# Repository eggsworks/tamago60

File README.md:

# tamago60

tamago60 is a hotswap, semi-split, low profile, ortholinear keyboard with a joystick in the middle.

## PCBWay

PCB prototyping for the tamago60 was kindly sponsored by [PCBWay](https://www.pcbway.com/). If you choose to build your own
tamago60, consider ordering from [PCBWay](https://www.pcbway.com/) to experience their fast turnaround, high quality production,
and excellent customer service. Thanks, PCBWay!

I've also shared this design on their site to make it really
easy to order your own board:

## Overview

We all love those laptops with the trackpoint in the middle of the keyboard, right? Influenced by that design,
with an ergo twist and a healthy dose of minimalism, the tamago60 is a roughly-60% board with a joystick
stuck between two semi-split ortho halves.

This design uses MX spacing (19mm) to allow flexibility with choice of keycaps. For the same reason, switches are
installed directly to the PCB rather than into a switchplate (DSA keycaps will crash into the plate if used with
Choc V2's).

## Components

- 60-64 Kailh Choc hotswap sockets
  - Depending on the keycaps you intend to use, you may need to install two switches in the 2u positions.
    If this is the case, only one is electrically connected and the other acts as a stabilizer. If your keycaps
    have the mounting position in the middle, you can just use the center position. Or, you can populate all three
    if you expect you might need to switch in the future.
- 60-62 Kailh Choc switches
  - Both original Choc and Choc V2 are supported.
- 61 SOD-123 SMD diodes (1N4148 or similar)
- 1 Pro Micro or compatible microcontroller module
- 1 K-Silver JP19 joystick module

A wireless build of this board has not yet been validated, but there are some features intended to improve quality-of-life
for any users who wish to try.

- Optional components for a wireless build:
  - 1 nice!nano, instead of the Pro Micro
  - 2 3216 SMD resistors (value can vary)
    - The intent of the resistors is to reduce the idle current drawn through the potentiometers of the joystick.
      If you are not doing a wireless build (or just don't care), populating 0 Ohm or simply bridging the contacts will suffice.
    - Too low resistance will increase idle power consumption, but two high may impact the ADC's ability to measure the
      joystick (e.g. 499k is too high).
  - 1 PCM12 SMD SPDT switch
    - This switch allows disconnecting the battery - if you don't care about the switch, but you still want to use the JST, you can
      bridge the pads intended for the switch.
  - 1 2-pin JST connector, if desired
    - If not using a JST connector for the battery, it can be soldered directly to the JST pads instead.
    - If using neither the the switch nor JST, you may as well attach the battery directly to the MCU module.

## Assembly

Prepare the back of the board with paste and place the SMT components:

- 61 diodes (cathode facing south)
- 60-64 sockets 
- Optionally, the two resistors

If you choose not to install the two resistors, you can simply bridge the pads intended for each.

Select two pads to bridge on the jumper near the joystick to choose whether the press action should be
a left or right click (it shares a position in the matrix with one of the keyswitches below it).

Use your preferred heating method to reflow, then move on to the THT components on the front of the board:

- Install the MCU socket
- Install the joystick

That's all there is to it! Install your switches and keycaps, flash the firmware, and your board is ready to use.

## Firmware

Firmware is available from [our fork of QMK](https://github.com/eggsworks/qmk_firmware/tree/tamago60).

## Accessories

Model files for a 3D-printable case are available in this repo.
The case is split in two parts in order to fit most beds. A cavity 
is provided in order to install a battery in the case of a wireless
build.

Install 8 M2 brass inserts in each half in order to mount the
PCB to the case.

## License

This repository is available under the terms of the [GPL, verison 3](LICENSE).

Some portions are derived from:

- [keyswitches.pretty](https://github.com/daprice/keyswitches.pretty) ([CC BY-SA 4.0](https://creativecommons.org/licenses/by-sa/4.0/))

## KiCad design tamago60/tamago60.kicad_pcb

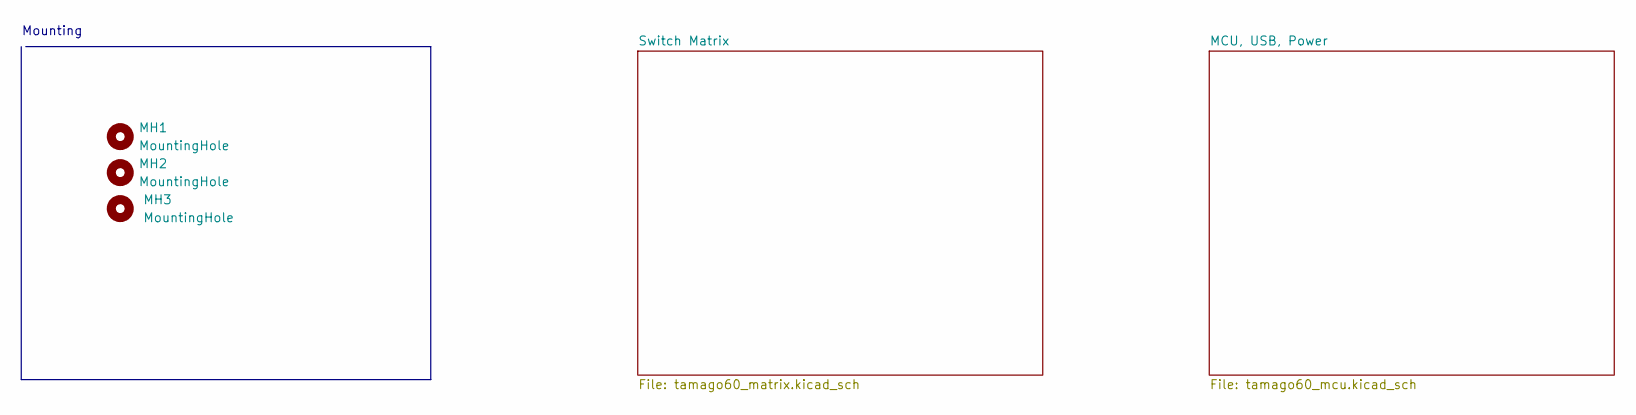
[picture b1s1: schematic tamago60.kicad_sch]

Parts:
MH1, MH3: MountingHole; oval_mounting_hole
MH2: MountingHole; circle_mounting_hole_npth

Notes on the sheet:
Mounting

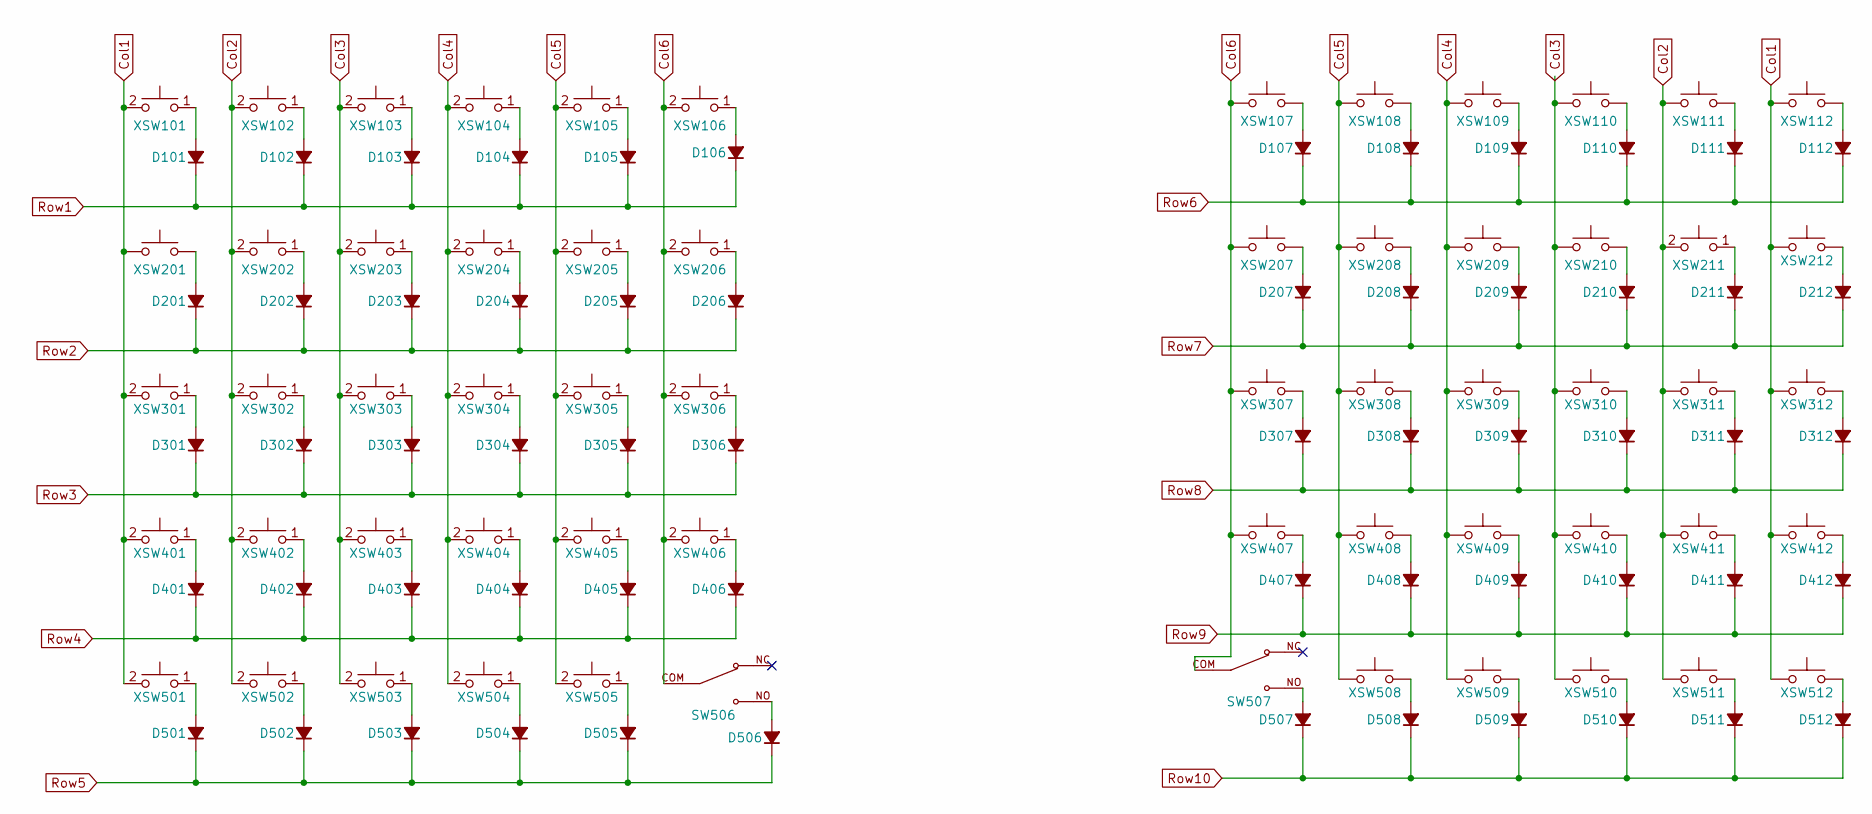
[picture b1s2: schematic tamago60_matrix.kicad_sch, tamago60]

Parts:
D101, D102, D103, D104, D105, D106, D107, D108, D109, D110, D111, D112, D201, D202, D203, D204, D205, D206, D207, D208, D209, D210, D211, D212, D301, D302, D303, D304, D305, D306, D307, D308, D309, D310, D311, D312, D401, D402, D403, D404, D405, D406, D407, D408, D409, D410, D411, D412, D501, D502, D503, D504, D505, D506, D507, D508, D509, D510, D511, D512: 1N1418; D_SOD-123
SW506, SW507: SW_D2F-FL; PARTREV N/A
XSW101, XSW102, XSW103, XSW104, XSW105, XSW106, XSW107, XSW108, XSW109, XSW110, XSW111, XSW112, XSW201, XSW202, XSW203, XSW204, XSW205, XSW206, XSW207, XSW208, XSW209, XSW210, XSW211, XSW212, XSW301, XSW302, XSW303, XSW304, XSW305, XSW306, XSW307, XSW308, XSW309, XSW310, XSW311, XSW312, XSW401, XSW402, XSW403, XSW404, XSW405, XSW406, XSW407, XSW408, XSW409, XSW410, XSW411, XSW412, XSW501, XSW502, XSW503, XSW504, XSW505, XSW508, XSW509, XSW510, XSW511, XSW512: Kailh choc socket; Kailh_socket_PG1350

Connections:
Col1: XSW101.2, XSW112.1, XSW201.1, XSW212.1, XSW301.2, XSW312.1, XSW401.2, XSW412.1, XSW501.2, XSW512.1; also elsewhere on the board
Col2: XSW102.2, XSW111.1, XSW202.2, XSW211.2, XSW302.2, XSW311.1, XSW402.2, XSW411.1, XSW502.2, XSW511.1; also elsewhere on the board
Col3: XSW103.2, XSW110.1, XSW203.2, XSW210.1, XSW303.2, XSW310.1, XSW403.2, XSW410.1, XSW503.2, XSW510.1; also elsewhere on the board
Col4: XSW104.2, XSW109.1, XSW204.2, XSW209.1, XSW304.2, XSW309.1, XSW404.2, XSW409.1, XSW504.2, XSW509.1; also elsewhere on the board
Col5: XSW105.2, XSW108.1, XSW205.2, XSW208.1, XSW305.2, XSW308.1, XSW405.2, XSW408.1, XSW505.2, XSW508.1; also elsewhere on the board
Col6: SW506.COM, SW507.COM, XSW106.2, XSW107.1, XSW206.2, XSW207.1, XSW306.2, XSW307.1, XSW406.2, XSW407.1; also elsewhere on the board
unnamed: D101.2 (A), XSW101.1
unnamed: D102.2 (A), XSW102.1
unnamed: D103.2 (A), XSW103.1
unnamed: D104.2 (A), XSW104.1
unnamed: D105.2 (A), XSW105.1
unnamed: D106.2 (A), XSW106.1
unnamed: D107.2 (A), XSW107.2
unnamed: D108.2 (A), XSW108.2
unnamed: D109.2 (A), XSW109.2
unnamed: D110.2 (A), XSW110.2
unnamed: D111.2 (A), XSW111.2
unnamed: D112.2 (A), XSW112.2
unnamed: D201.2 (A), XSW201.2
unnamed: D202.2 (A), XSW202.1
unnamed: D203.2 (A), XSW203.1
unnamed: D204.2 (A), XSW204.1
unnamed: D205.2 (A), XSW205.1
unnamed: D206.2 (A), XSW206.1
unnamed: D207.2 (A), XSW207.2
unnamed: D208.2 (A), XSW208.2
unnamed: D209.2 (A), XSW209.2
unnamed: D210.2 (A), XSW210.2
unnamed: D211.2 (A), XSW211.1
unnamed: D212.2 (A), XSW212.2
unnamed: D301.2 (A), XSW301.1
unnamed: D302.2 (A), XSW302.1
unnamed: D303.2 (A), XSW303.1
unnamed: D304.2 (A), XSW304.1
unnamed: D305.2 (A), XSW305.1
unnamed: D306.2 (A), XSW306.1
unnamed: D307.2 (A), XSW307.2
unnamed: D308.2 (A), XSW308.2
unnamed: D309.2 (A), XSW309.2
unnamed: D310.2 (A), XSW310.2
unnamed: D311.2 (A), XSW311.2
unnamed: D312.2 (A), XSW312.2
unnamed: D401.2 (A), XSW401.1
unnamed: D402.2 (A), XSW402.1
unnamed: D403.2 (A), XSW403.1
unnamed: D404.2 (A), XSW404.1
unnamed: D405.2 (A), XSW405.1
unnamed: D406.2 (A), XSW406.1
unnamed: D407.2 (A), XSW407.2
unnamed: D408.2 (A), XSW408.2
unnamed: D409.2 (A), XSW409.2
unnamed: D410.2 (A), XSW410.2
unnamed: D411.2 (A), XSW411.2
unnamed: D412.2 (A), XSW412.2
unnamed: D501.2 (A), XSW501.1
unnamed: D502.2 (A), XSW502.1
unnamed: D503.2 (A), XSW503.1
unnamed: D504.2 (A), XSW504.1
unnamed: D505.2 (A), XSW505.1
unnamed: D506.2 (A), SW506.NO
unnamed: D507.2 (A), SW507.NO
unnamed: D508.2 (A), XSW508.2
unnamed: D509.2 (A), XSW509.2
unnamed: D510.2 (A), XSW510.2
unnamed: D511.2 (A), XSW511.2
unnamed: D512.2 (A), XSW512.2
Row1: D101.1 (K), D102.1 (K), D103.1 (K), D104.1 (K), D105.1 (K), D106.1 (K); also elsewhere on the board
Row2: D201.1 (K), D202.1 (K), D203.1 (K), D204.1 (K), D205.1 (K), D206.1 (K); also elsewhere on the board
Row3: D301.1 (K), D302.1 (K), D303.1 (K), D304.1 (K), D305.1 (K), D306.1 (K); also elsewhere on the board
Row4: D401.1 (K), D402.1 (K), D403.1 (K), D404.1 (K), D405.1 (K), D406.1 (K); also elsewhere on the board
Row5: D501.1 (K), D502.1 (K), D503.1 (K), D504.1 (K), D505.1 (K), D506.1 (K); also elsewhere on the board
Row6: D107.1 (K), D108.1 (K), D109.1 (K), D110.1 (K), D111.1 (K), D112.1 (K); also elsewhere on the board
Row7: D207.1 (K), D208.1 (K), D209.1 (K), D210.1 (K), D211.1 (K), D212.1 (K); also elsewhere on the board
Row8: D307.1 (K), D308.1 (K), D309.1 (K), D310.1 (K), D311.1 (K), D312.1 (K); also elsewhere on the board
Row9: D407.1 (K), D408.1 (K), D409.1 (K), D410.1 (K), D411.1 (K), D412.1 (K); also elsewhere on the board
Row10: D507.1 (K), D508.1 (K), D509.1 (K), D510.1 (K), D511.1 (K), D512.1 (K); also elsewhere on the board

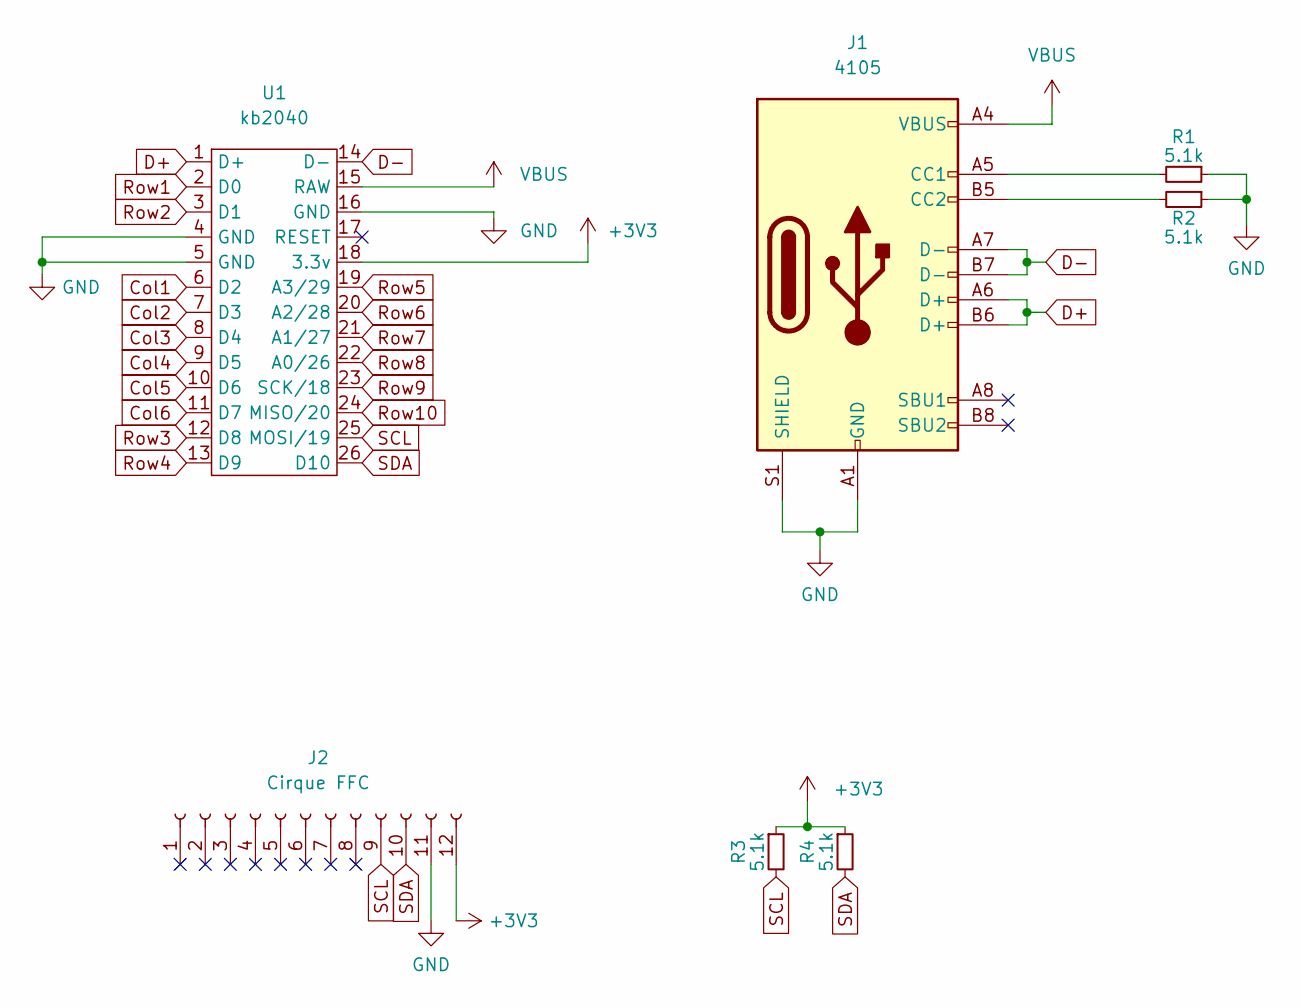
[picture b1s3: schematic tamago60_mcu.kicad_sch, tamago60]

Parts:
J1: 4105; USB_C_Receptacle_GCT_USB4105-xx-A_16P_TopMnt_Horizontal
J2: Cirque FFC; Hirose_FH12-12S-0.5SH_1x12-1MP_P0.50mm_Horizontal
R1, R2, R3, R4: 5.1k; R_1206_3216Metric
U1: kb2040

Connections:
+3V3: J2.12, R3.1, R4.1, U1.18 (3.3v)
Col1: U1.6 (D2); also elsewhere on the board
Col2: U1.7 (D3); also elsewhere on the board
Col3: U1.8 (D4); also elsewhere on the board
Col4: U1.9 (D5); also elsewhere on the board
Col5: U1.10 (D6); also elsewhere on the board
Col6: U1.11 (D7); also elsewhere on the board
D+: J1.A6 (D+), J1.B6 (D+), U1.1 (D+)
D-: J1.A7 (D-), J1.B7 (D-), U1.14 (D-)
GND: J1.A1 (GND), J1.A12 (GND), J1.B1 (GND), J1.B12 (GND), J1.S1 (SHIELD), J2.11, R1.1, R2.1, U1.4 (GND), U1.5 (GND), U1.16 (GND)
unnamed: J1.A5 (CC1), R1.2
unnamed: J1.B5 (CC2), R2.2
Row1: U1.2 (D0); also elsewhere on the board
Row2: U1.3 (D1); also elsewhere on the board
Row3: U1.12 (D8); also elsewhere on the board
Row4: U1.13 (D9); also elsewhere on the board
Row5: U1.19 (A3/29); also elsewhere on the board
Row6: U1.20 (A2/28); also elsewhere on the board
Row7: U1.21 (A1/27); also elsewhere on the board
Row8: U1.22 (A0/26); also elsewhere on the board
Row9: U1.23 (SCK/18); also elsewhere on the board
Row10: U1.24 (MISO/20); also elsewhere on the board
SCL: J2.9, R3.2, U1.25 (MOSI/19)
SDA: J2.10, R4.2, U1.26 (D10)
VBUS: J1.A4 (VBUS), J1.A9 (VBUS), J1.B4 (VBUS), J1.B9 (VBUS), U1.15 (RAW)

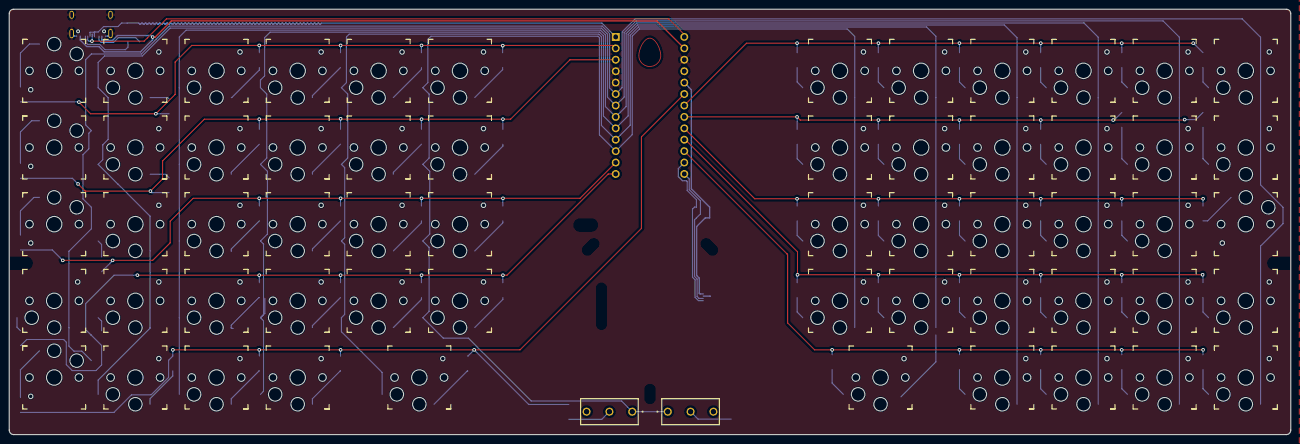
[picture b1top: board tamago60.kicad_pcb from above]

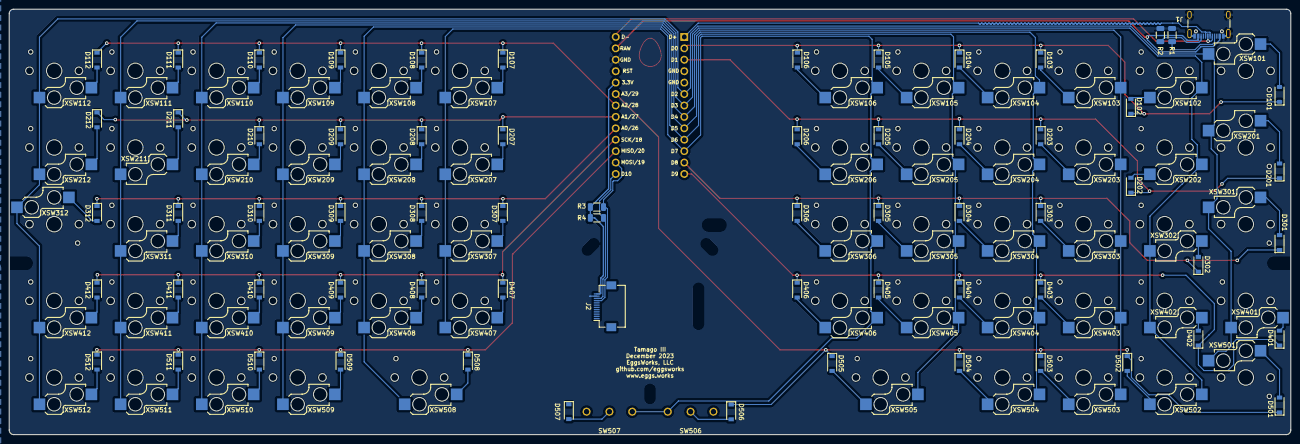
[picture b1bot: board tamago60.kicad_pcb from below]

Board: 2 copper layers, 285.0 x 94.6 mm, 189 parts (66 on the bottom side), 85 nets.

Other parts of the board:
A1: cirque_mounting_35mm
SW101, SW102, SW103, SW104, SW105, SW106, SW107, SW108, SW109, SW110, SW111, SW112, SW201, SW202, SW203, SW204, SW205, SW206, SW207, SW208, SW209, SW210, SW211, SW212, SW301, SW302, SW303, SW304, SW305, SW306, SW307, SW308, SW309, SW310, SW311, SW312, SW401, SW402, SW403, SW404, SW405, SW406, SW407, SW408, SW409, SW410, SW411, SW412, SW501, SW502, SW503, SW504, SW505, SW508, SW509, SW510, SW511, SW512: Kailh MX socket; Kailh_socket_PG1350_position

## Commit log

2023-04-13 Initial design
2023-04-14 Finalize v1 design
2023-04-14 Create LICENSE
2023-04-14 Fix 2u position defect - bump to v1.1
2023-04-14 Add readme
2023-04-14 Add images
2023-04-14 Fix Choc V2 locating hole support in 2u positions
2023-04-14 Fix typo
2023-04-22 Add assembly instructions to readme
2023-04-22 Add license information to readme
2023-04-22 Add missed instruction for selecting L/R action of joystick press
2023-04-23 Move ref silkscreen for joystick somewhere it will be hidden
2023-04-23 Replace JST with 2mm, move its position; update schematic to be consistent with PCB
2023-04-25 Add models for case
2023-04-25 Add PCBWay project link
2023-05-24 Initial layout for tamago v2
2023-05-25 route left side
2023-08-30 rework with rp2040 module
2023-08-30 mfgr prep
2023-09-01 fixes for production
2023-09-30 layout with choc sockets
2023-12-18 routing
2026-06-20 add trackpad holder
